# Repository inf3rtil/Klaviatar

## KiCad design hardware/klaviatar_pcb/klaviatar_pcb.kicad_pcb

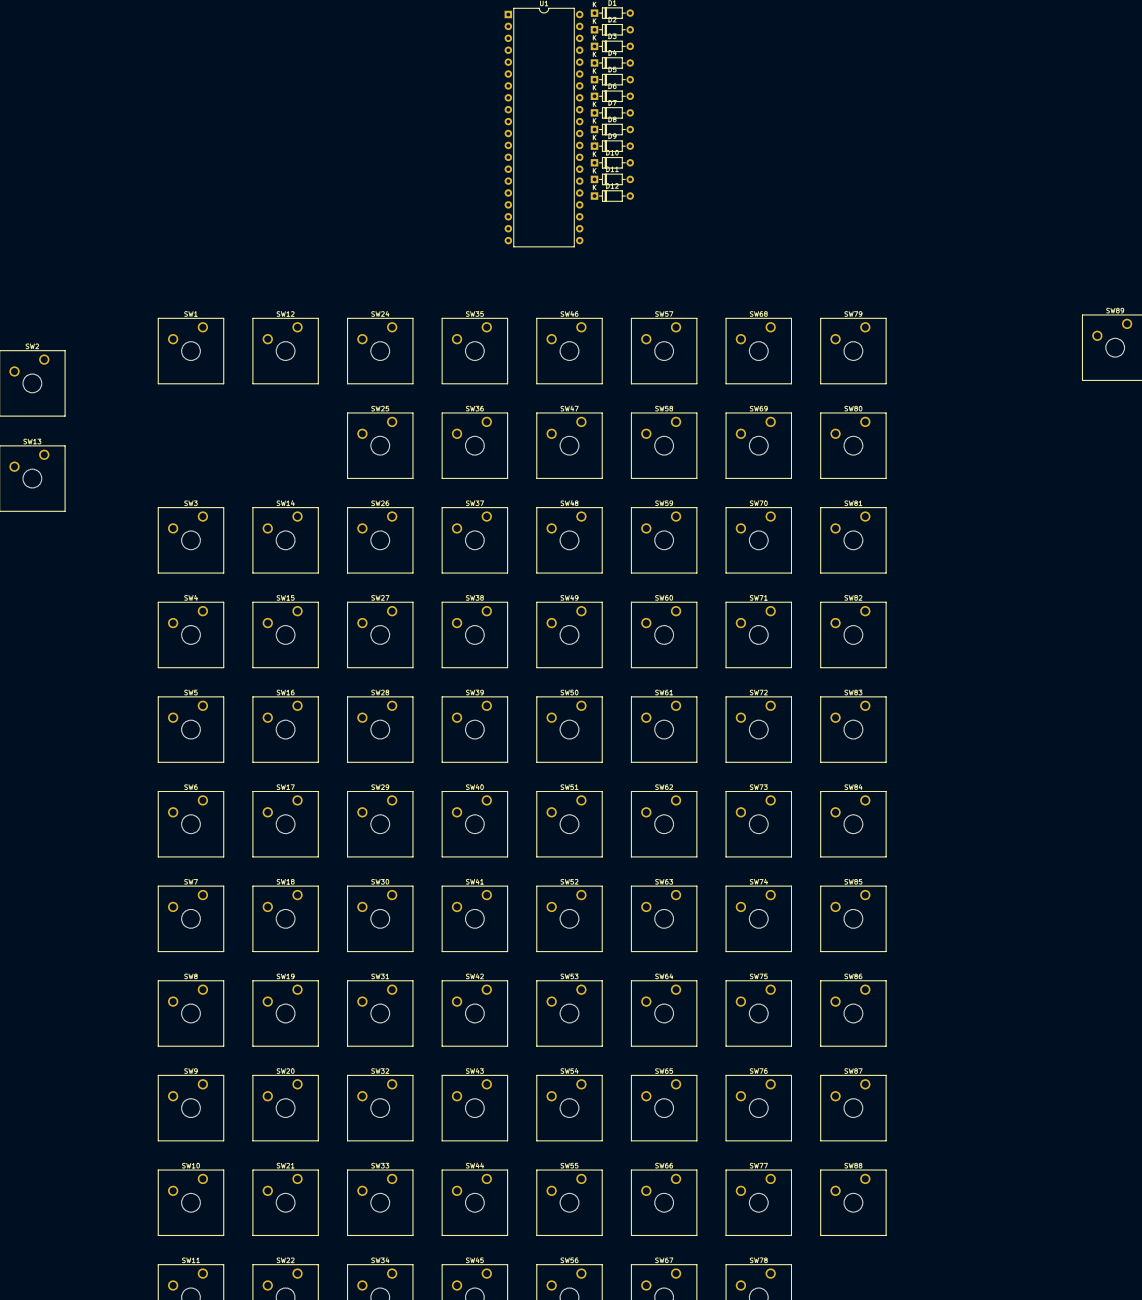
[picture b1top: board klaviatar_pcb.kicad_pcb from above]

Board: 2 copper layers, 101 parts (0 on the bottom side), 21 nets, no tracks yet.

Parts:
D1, D2, D3, D4, D5, D6, D7, D8, D9, D10, D11, D12: 1N4148; D_DO-35_SOD27_P7.62mm_Horizontal
SW1: "-"; SW_Cherry_MX_1.00u_Plate
SW2: ESC; SW_Cherry_MX_1.00u_Plate
SW3, SW4, SW5, SW6, SW7, SW8, SW9, SW10, SW11, SW12, SW13, SW14, SW15, SW16, SW17, SW18, SW19, SW20, SW21, SW22, SW24, SW25, SW26, SW27, SW28, SW29, SW30, SW31, SW32, SW33, SW34, SW35, SW36, SW37, SW38, SW39, SW40, SW41, SW42, SW44, SW45, SW46, SW47, SW48, SW49, SW50, SW51, SW52, SW53, SW54, SW55, SW56, SW57, SW58, SW59, SW60, SW61, SW62, SW63, SW64, SW65, SW66, SW67, SW68, SW69, SW70, SW71, SW72, SW73, SW74, SW75, SW76, SW77, SW78, SW79, SW80, SW81, SW82, SW83, SW84, SW85, SW86, SW87, SW88: SA1; SW_Cherry_MX_1.00u_Plate
SW43: L; SW_Cherry_MX_1.00u_Plate
SW89: F10; SW_Cherry_MX_1.00u_Plate
U1: PIC18F4550-IP; DIP-40_W15.24mm

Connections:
/Keyboard/XT1_{1}: SW1.2, SW12.2, SW24.2, SW45.2, SW46.2, SW47.2, SW48.2
/Keyboard/XT1_{2}: SW2.2, SW13.2, SW25.2, SW26.2, SW49.2, SW50.2, SW51.2, SW52.2
/Keyboard/XT1_{3}: SW3.2, SW14.2, SW27.2, SW28.2, SW53.2, SW54.2, SW55.2, SW56.2
/Keyboard/XT1_{4}: SW4.2, SW15.2, SW29.2, SW30.2, SW57.2, SW58.2, SW59.2, SW60.2
/Keyboard/XT1_{5}: SW5.2, SW16.2, SW31.2, SW32.2, SW61.2, SW62.2, SW63.2, SW64.2
/Keyboard/XT1_{6}: SW6.2, SW17.2, SW33.2, SW34.2, SW65.2, SW66.2, SW67.2, SW68.2
/Keyboard/XT1_{7}: SW7.2, SW18.2, SW35.2, SW36.2, SW69.2, SW70.2, SW71.2, SW72.2
/Keyboard/XT1_{8}: SW8.2, SW19.2, SW37.2, SW38.2, SW73.2, SW74.2, SW75.2, SW76.2
/Keyboard/XT1_{9}: SW9.2, SW20.2, SW39.2, SW40.2, SW77.2, SW78.2, SW79.2, SW80.2
/Keyboard/XT1_{10}: SW10.2, SW21.2, SW41.2, SW42.2, SW81.2, SW82.2, SW83.2, SW84.2
/Keyboard/XT1_{11}: SW11.2, SW22.2, SW43.2, SW44.2, SW85.2, SW86.2, SW87.2, SW88.2
/Keyboard/XT2_{1}: SW1.1, SW2.1, SW3.1, SW4.1, SW5.1, SW6.1, SW7.1, SW8.1, SW9.1, SW10.1, SW11.1
/Keyboard/XT2_{2}: SW12.1, SW13.1, SW14.1, SW15.1, SW16.1, SW17.1, SW18.1, SW19.1, SW20.1, SW21.1, SW22.1
/Keyboard/XT2_{3}: SW25.1, SW27.1, SW29.1, SW31.1, SW33.1, SW35.1, SW37.1, SW39.1, SW41.1, SW43.1
/Keyboard/XT2_{4}: SW24.1, SW26.1, SW28.1, SW30.1, SW32.1, SW34.1, SW36.1, SW38.1, SW40.1, SW42.1, SW44.1
/Keyboard/XT2_{5}: SW45.1, SW49.1, SW53.1, SW57.1, SW61.1, SW65.1, SW69.1, SW73.1, SW77.1, SW81.1, SW85.1
/Keyboard/XT2_{6}: SW46.1, SW50.1, SW54.1, SW58.1, SW62.1, SW66.1, SW70.1, SW74.1, SW78.1, SW82.1, SW86.1
/Keyboard/XT2_{7}: SW47.1, SW51.1, SW55.1, SW59.1, SW63.1, SW67.1, SW71.1, SW75.1, SW79.1, SW83.1, SW87.1
/Keyboard/XT2_{8}: SW48.1, SW52.1, SW56.1, SW60.1, SW64.1, SW68.1, SW72.1, SW76.1, SW80.1, SW84.1, SW88.1
GND: U1.12 (VSS), U1.31 (VSS)
unnamed: U1.11 (VDD), U1.32 (VDD)

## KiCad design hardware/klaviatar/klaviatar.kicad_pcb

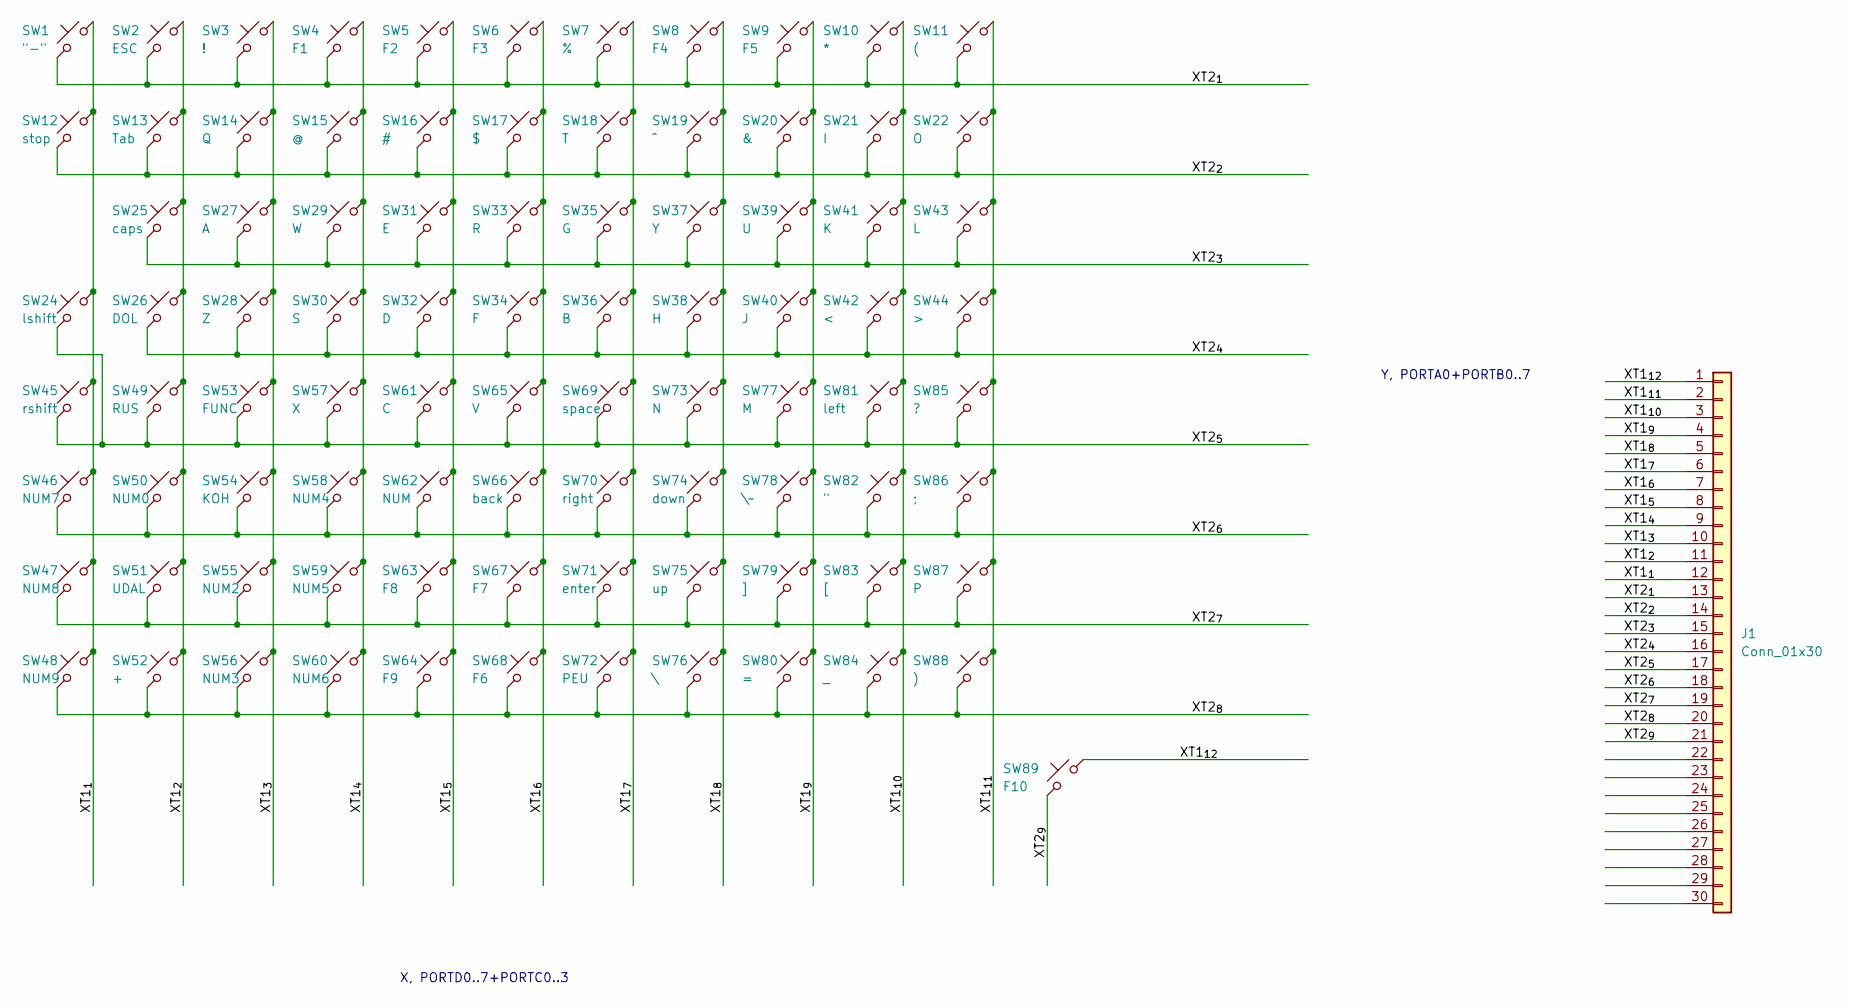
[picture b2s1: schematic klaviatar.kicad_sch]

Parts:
J1: Conn_01x30; PinHeader_1x30_P2.54mm_Vertical
SW1: "-"; SW_Cherry_MX_1.00u_Plate
SW2: ESC; SW_Cherry_MX_1.00u_Plate
SW3: !; SW_Cherry_MX_1.00u_Plate
SW4: F1; SW_Cherry_MX_1.00u_Plate
SW5: F2; SW_Cherry_MX_1.00u_Plate
SW6: F3; SW_Cherry_MX_1.00u_Plate
SW7: %; SW_Cherry_MX_1.00u_Plate
SW8: F4; SW_Cherry_MX_1.00u_Plate
SW9: F5; SW_Cherry_MX_1.00u_Plate
SW10: *; SW_Cherry_MX_1.00u_Plate
SW11: (; SW_Cherry_MX_1.00u_Plate
SW12: stop; SW_Cherry_MX_1.00u_Plate
SW13: Tab; SW_Cherry_MX_1.00u_Plate
SW14: Q; SW_Cherry_MX_1.00u_Plate
SW15: @; SW_Cherry_MX_1.00u_Plate
SW16: #; SW_Cherry_MX_1.00u_Plate
SW17: $; SW_Cherry_MX_1.00u_Plate
SW18: T; SW_Cherry_MX_1.00u_Plate
SW19: ^; SW_Cherry_MX_1.00u_Plate
SW20: &; SW_Cherry_MX_1.00u_Plate
SW21: I; SW_Cherry_MX_1.00u_Plate
SW22: O; SW_Cherry_MX_1.00u_Plate
SW24: lshift; SW_Cherry_MX_1.00u_Plate
SW25: caps; SW_Cherry_MX_1.00u_Plate
SW26: DOL; SW_Cherry_MX_1.00u_Plate
SW27: A; SW_Cherry_MX_1.00u_Plate
SW28: Z; SW_Cherry_MX_1.00u_Plate
SW29: W; SW_Cherry_MX_1.00u_Plate
SW30: S; SW_Cherry_MX_1.00u_Plate
SW31: E; SW_Cherry_MX_1.00u_Plate
SW32: D; SW_Cherry_MX_1.00u_Plate
SW33: R; SW_Cherry_MX_1.00u_Plate
SW34: F; SW_Cherry_MX_1.00u_Plate
SW35: G; SW_Cherry_MX_1.00u_Plate
SW36: B; SW_Cherry_MX_1.00u_Plate
SW37: Y; SW_Cherry_MX_1.00u_Plate
SW38: H; SW_Cherry_MX_1.00u_Plate
SW39: U; SW_Cherry_MX_1.00u_Plate
SW40: J; SW_Cherry_MX_1.00u_Plate
SW41: K; SW_Cherry_MX_1.00u_Plate
SW42: <; SW_Cherry_MX_1.00u_Plate
SW43: L; SW_Cherry_MX_1.00u_Plate
SW44: >; SW_Cherry_MX_1.00u_Plate
SW45: rshift; SW_Cherry_MX_1.00u_Plate
SW46: NUM7; SW_Cherry_MX_1.00u_Plate
SW47: NUM8; SW_Cherry_MX_1.00u_Plate
SW48: NUM9; SW_Cherry_MX_1.00u_Plate
SW49: RUS; SW_Cherry_MX_1.00u_Plate
SW50: NUM0; SW_Cherry_MX_1.00u_Plate
SW51: UDAL; SW_Cherry_MX_1.00u_Plate
SW52: +; SW_Cherry_MX_1.00u_Plate
SW53: FUNC; SW_Cherry_MX_1.00u_Plate
SW54: KOH; SW_Cherry_MX_1.00u_Plate
SW55: NUM2; SW_Cherry_MX_1.00u_Plate
SW56: NUM3; SW_Cherry_MX_1.00u_Plate
SW57: X; SW_Cherry_MX_1.00u_Plate
SW58: NUM4; SW_Cherry_MX_1.00u_Plate
SW59: NUM5; SW_Cherry_MX_1.00u_Plate
SW60: NUM6; SW_Cherry_MX_1.00u_Plate
SW61: C; SW_Cherry_MX_1.00u_Plate
SW62: NUM; SW_Cherry_MX_1.00u_Plate
SW63: F8; SW_Cherry_MX_1.00u_Plate
SW64: F9; SW_Cherry_MX_1.00u_Plate
SW65: V; SW_Cherry_MX_1.00u_Plate
SW66: back; SW_Cherry_MX_1.00u_Plate
SW67: F7; SW_Cherry_MX_1.00u_Plate
SW68: F6; SW_Cherry_MX_1.00u_Plate
SW69: space; SW_Cherry_MX_1.00u_Plate
SW70: right; SW_Cherry_MX_1.00u_Plate
SW71: enter; SW_Cherry_MX_1.00u_Plate
SW72: PEU; SW_Cherry_MX_1.00u_Plate
SW73: N; SW_Cherry_MX_1.00u_Plate
SW74: down; SW_Cherry_MX_1.00u_Plate
SW75: up; SW_Cherry_MX_1.00u_Plate
SW76: \; SW_Cherry_MX_1.00u_Plate
SW77: M; SW_Cherry_MX_1.00u_Plate
SW78: \~; SW_Cherry_MX_1.00u_Plate
SW79: ]; SW_Cherry_MX_1.00u_Plate
SW80: =; SW_Cherry_MX_1.00u_Plate
SW81: left; SW_Cherry_MX_1.00u_Plate
SW82: "; SW_Cherry_MX_1.00u_Plate
SW83: [; SW_Cherry_MX_1.00u_Plate
SW84: _; SW_Cherry_MX_1.00u_Plate
SW85: ?; SW_Cherry_MX_1.00u_Plate
SW86: ;; SW_Cherry_MX_1.00u_Plate
SW87: P; SW_Cherry_MX_1.00u_Plate
SW88: ); SW_Cherry_MX_1.00u_Plate
SW89: F10; SW_Cherry_MX_1.00u_Plate

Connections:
/XT1_{1}: J1.12, SW1.2, SW12.2, SW24.2, SW45.2, SW46.2, SW47.2, SW48.2
/XT1_{2}: J1.11, SW2.2, SW13.2, SW25.2, SW26.2, SW49.2, SW50.2, SW51.2, SW52.2
/XT1_{3}: J1.10, SW3.2, SW14.2, SW27.2, SW28.2, SW53.2, SW54.2, SW55.2, SW56.2
/XT1_{4}: J1.9, SW4.2, SW15.2, SW29.2, SW30.2, SW57.2, SW58.2, SW59.2, SW60.2
/XT1_{5}: J1.8, SW5.2, SW16.2, SW31.2, SW32.2, SW61.2, SW62.2, SW63.2, SW64.2
/XT1_{6}: J1.7, SW6.2, SW17.2, SW33.2, SW34.2, SW65.2, SW66.2, SW67.2, SW68.2
/XT1_{7}: J1.6, SW7.2, SW18.2, SW35.2, SW36.2, SW69.2, SW70.2, SW71.2, SW72.2
/XT1_{8}: J1.5, SW8.2, SW19.2, SW37.2, SW38.2, SW73.2, SW74.2, SW75.2, SW76.2
/XT1_{9}: J1.4, SW9.2, SW20.2, SW39.2, SW40.2, SW77.2, SW78.2, SW79.2, SW80.2
/XT1_{10}: J1.3, SW10.2, SW21.2, SW41.2, SW42.2, SW81.2, SW82.2, SW83.2, SW84.2
/XT1_{11}: J1.2, SW11.2, SW22.2, SW43.2, SW44.2, SW85.2, SW86.2, SW87.2, SW88.2
/XT1_{12}: J1.1, SW89.2
/XT2_{1}: J1.13, SW1.1, SW2.1, SW3.1, SW4.1, SW5.1, SW6.1, SW7.1, SW8.1, SW9.1, SW10.1, SW11.1
/XT2_{2}: J1.14, SW12.1, SW13.1, SW14.1, SW15.1, SW16.1, SW17.1, SW18.1, SW19.1, SW20.1, SW21.1, SW22.1
/XT2_{3}: J1.15, SW25.1, SW27.1, SW29.1, SW31.1, SW33.1, SW35.1, SW37.1, SW39.1, SW41.1, SW43.1
/XT2_{4}: J1.16, SW26.1, SW28.1, SW30.1, SW32.1, SW34.1, SW36.1, SW38.1, SW40.1, SW42.1, SW44.1
/XT2_{5}: J1.17, SW24.1, SW45.1, SW49.1, SW53.1, SW57.1, SW61.1, SW65.1, SW69.1, SW73.1, SW77.1, SW81.1, SW85.1
/XT2_{6}: J1.18, SW46.1, SW50.1, SW54.1, SW58.1, SW62.1, SW66.1, SW70.1, SW74.1, SW78.1, SW82.1, SW86.1
/XT2_{7}: J1.19, SW47.1, SW51.1, SW55.1, SW59.1, SW63.1, SW67.1, SW71.1, SW75.1, SW79.1, SW83.1, SW87.1
/XT2_{8}: J1.20, SW48.1, SW52.1, SW56.1, SW60.1, SW64.1, SW68.1, SW72.1, SW76.1, SW80.1, SW84.1, SW88.1
/XT2_{9}: J1.21, SW89.1

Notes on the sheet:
X, PORTD0..7+PORTC0..3
Y, PORTA0+PORTB0..7

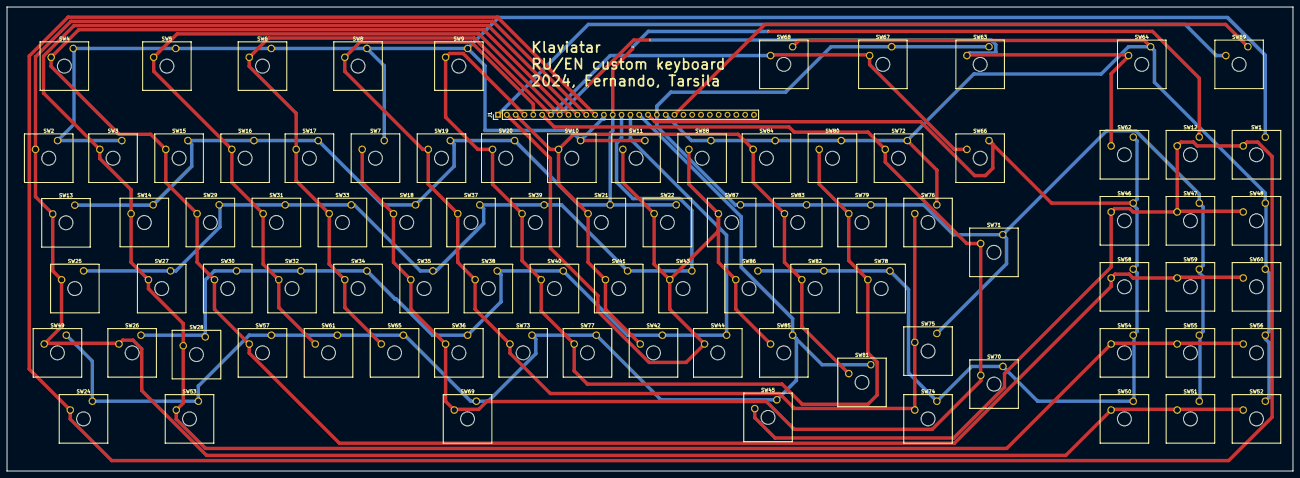
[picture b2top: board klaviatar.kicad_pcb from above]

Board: 2 copper layers, 370.0 x 133.5 mm, 89 parts (0 on the bottom side), 21 nets.

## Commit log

2023-07-20 first POC
2023-07-20 keymap impl
2023-07-20 PCB design init
2023-07-27 working letters
2023-07-28 first working version
2023-07-29 fix timers
2023-07-30 change layout
2023-07-30 handle key press
2023-07-30 update badge
2023-08-03 replace 74hc595
2023-08-03 using pic for scan keys
2023-08-04 keyboard pcb
2023-08-04 fix bug in PORTD bit 7
2023-08-05 press more than one key
2023-08-08 fix keymap
2023-08-08 add connections
2023-08-17 update arduino source
2023-08-18 update gitignore
2023-08-18 update sch
2024-07-07 add custom pcb
